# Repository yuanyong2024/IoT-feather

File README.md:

### This is a BG95 EVB in adafruit feather form-factor.
### It can be developed by quecpython, similar to circuit python

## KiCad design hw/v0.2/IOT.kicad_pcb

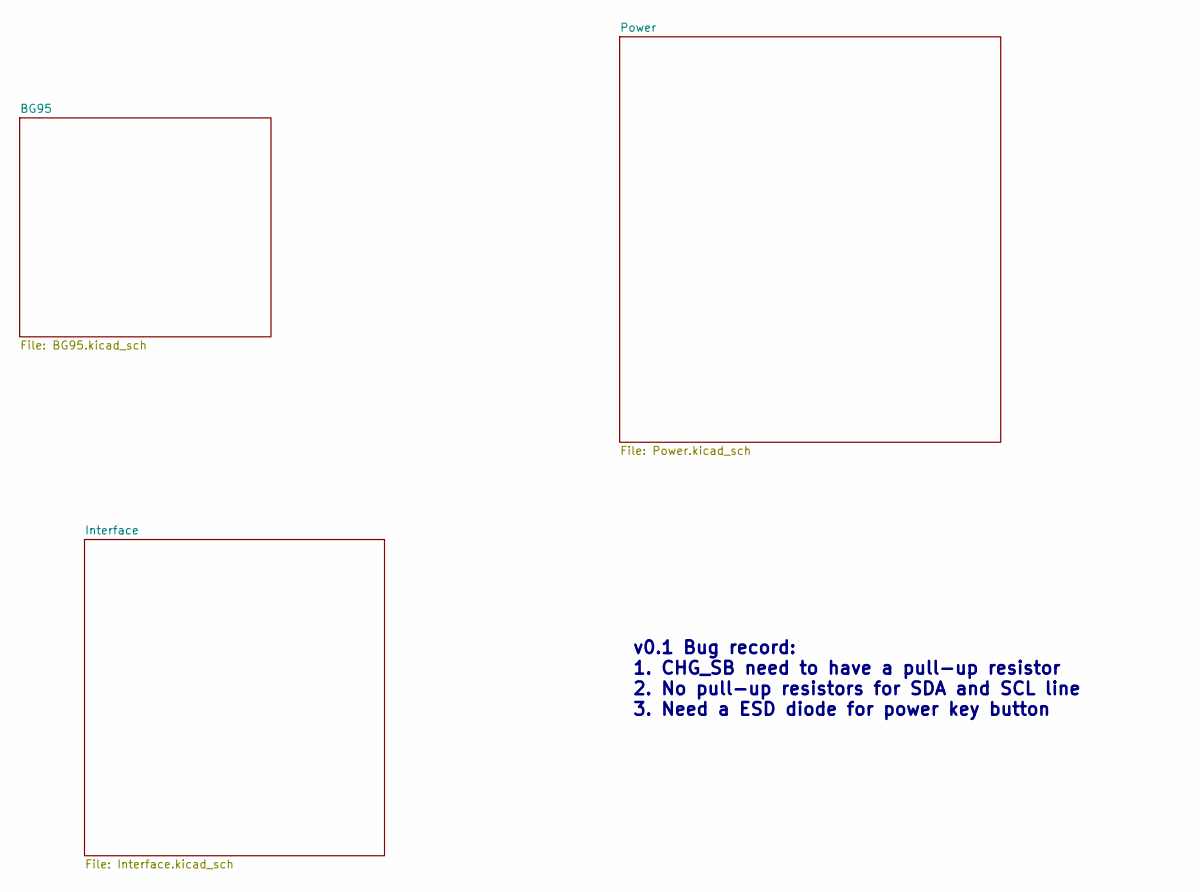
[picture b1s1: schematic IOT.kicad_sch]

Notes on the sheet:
v0.1 Bug record: 1. CHG_SB need to have a pull-up resistor 2. No pull-up resistors for SDA and SCL line 3. Need a ESD diode for power key button

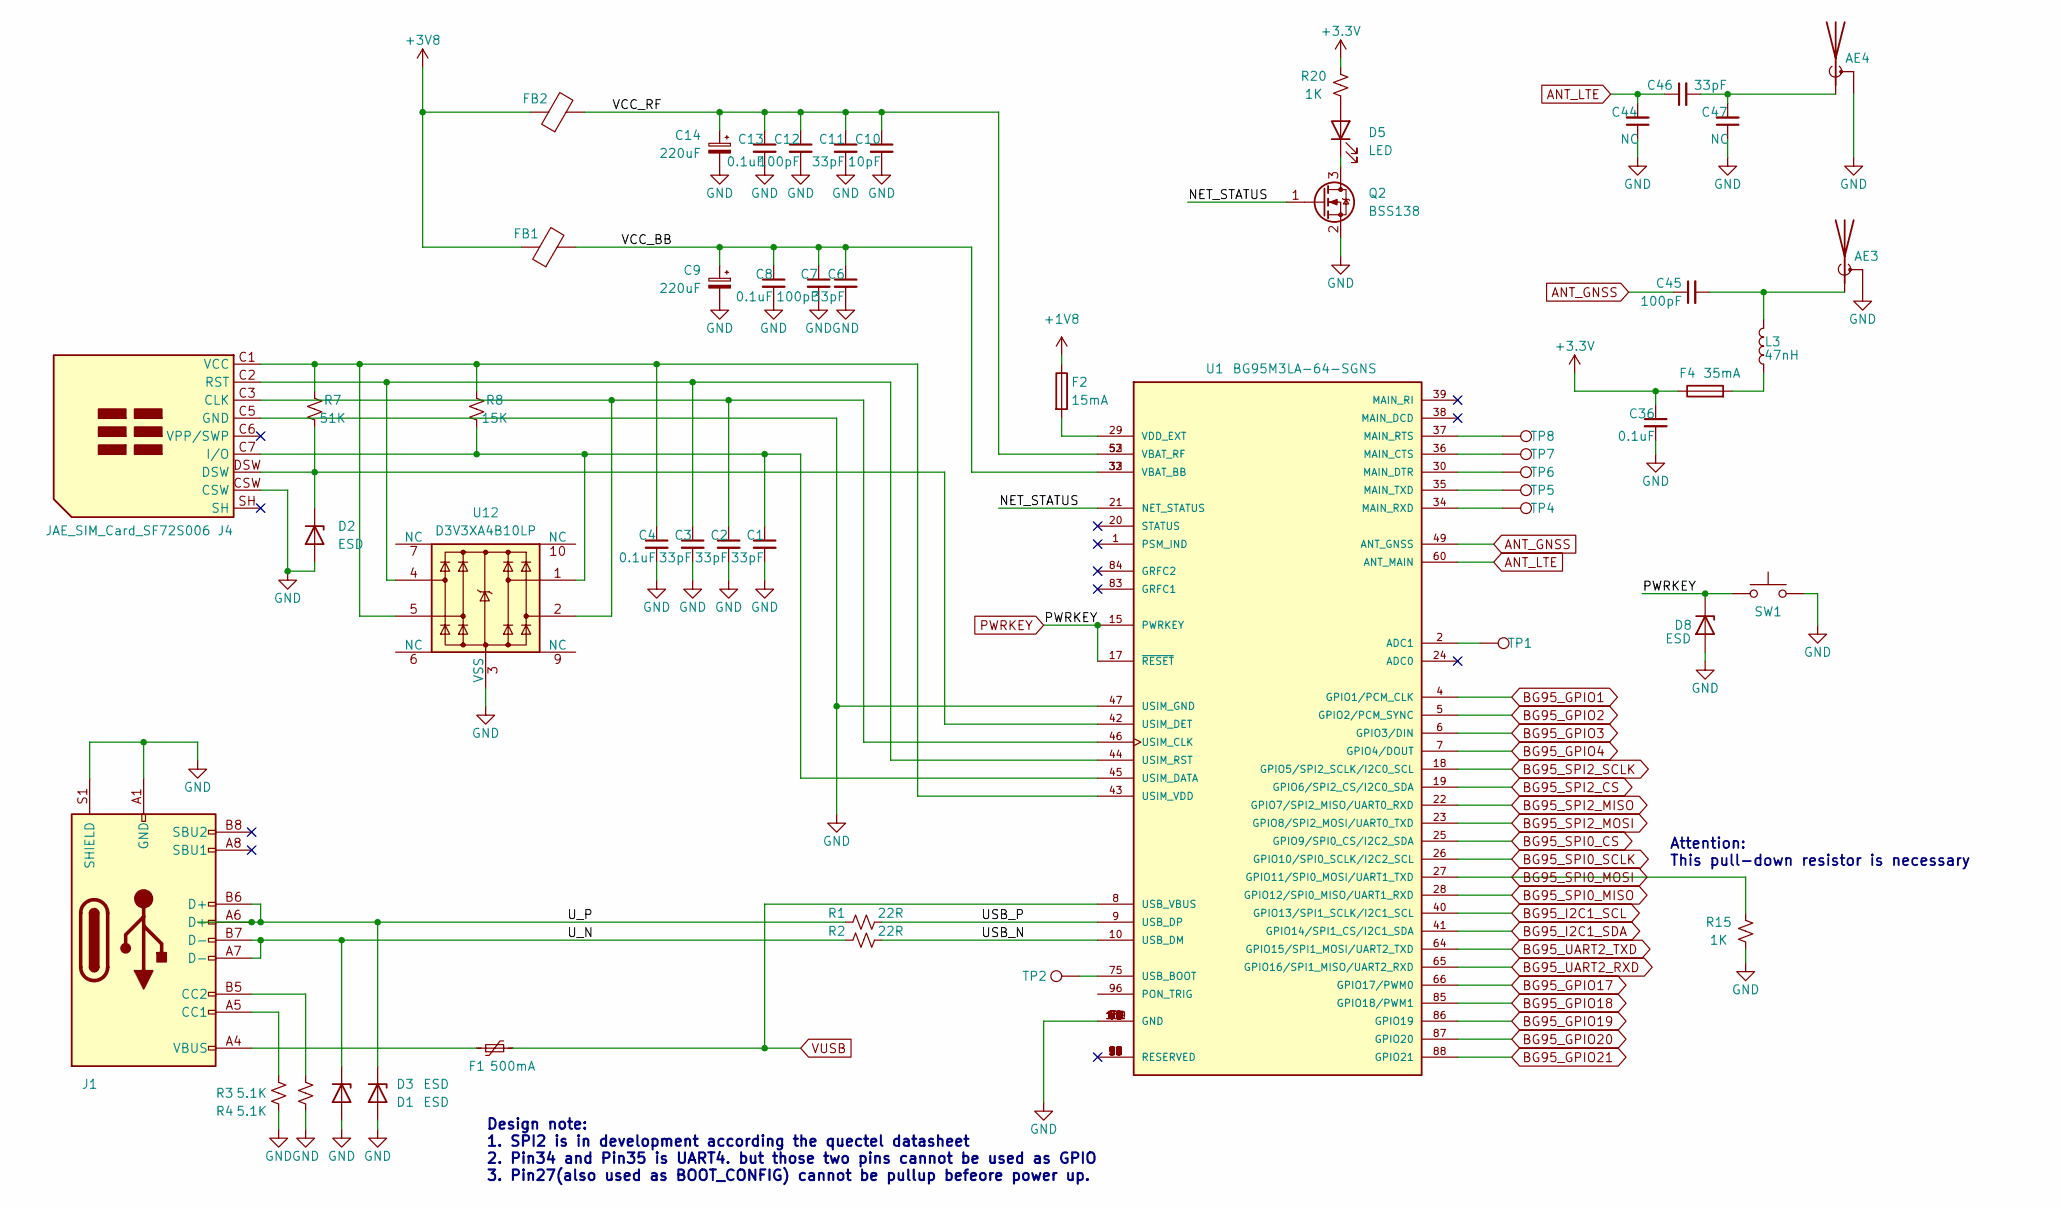
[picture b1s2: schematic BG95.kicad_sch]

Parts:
AE3, AE4: Antenna_Shield; U.FL_Hirose_U.FL-R-SMT-1_Vertical
C1, C2, C3, C6, C11: 33pF; C_0402_1005Metric
C4, C8, C13, C36: 0.1uF; C_0402_1005Metric
C7, C12: 100pF; C_0402_1005Metric
C9, C14: 220uF; CP_EIA-3528-12_Kemet-T
C10: 10pF; C_0402_1005Metric
C44, C47: NC; C_0201_0603Metric
C45: 100pF; C_0201_0603Metric
C46: 33pF; C_0201_0603Metric
D1, D2, D3: ESD; D_SOD-923
D5: LED; LED_0603_1608Metric
D8: ESD; D_SOD-523
F1: 500mA; Fuse_0603_1608Metric
F2: 15mA; Fuse_0402_1005Metric
F4: 35mA; Fuse_0402_1005Metric
FB1, FB2: L_0603_1608Metric
J1: USB_C_Receptacle_USB2.0; USB_C_Receptacle_HRO_TYPE-C-31-M-12
J4: JAE_SIM_Card_SF72S006
L3: 47nH; L_0402_1005Metric
Q2: BSS138; SOT-523
R1, R2: 22R; R_0402_1005Metric
R3, R4: 5.1K; R_0402_1005Metric
R7: 51K; R_0402_1005Metric
R8: 15K; R_0402_1005Metric
R15, R20: 1K; R_0402_1005Metric
SW1: SW_Omron_B3FS; SW_Push_SPST_NO_Alps_SKRK
TP1, TP2, TP4, TP5, TP6, TP7, TP8: TestPoint; TestPoint_Pad_D1.0mm
U1: BG95M3LA-64-SGNS; XCVR_BG95M3LA-64-SGNS
U12: D3V3XA4B10LP; Diodes_UDFN-10_1.0x2.5mm_P0.5mm

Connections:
+1V8: F2.1; also elsewhere on the board
+3V8: FB1.1, FB2.1; also elsewhere on the board
/BG95/NET_STATUS: Q2.1 (G), U1.21 (NET_STATUS)
/BG95/USB_N: R2.2, U1.10 (USB_DM)
/BG95/USB_P: R1.2, U1.9 (USB_DP)
/BG95/U_N: D1.1 (K), J1.A7 (D-), J1.B7 (D-), R2.1
/BG95/U_P: D3.1 (K), J1.A6 (D+), J1.B6 (D+), R1.1
/BG95/VCC_BB: C6.1, C7.1, C8.1, C9.1, FB1.2, U1.32 (VBAT_BB), U1.33 (VBAT_BB)
/BG95/VCC_RF: C10.1, C11.1, C12.1, C13.1, C14.1, FB2.2, U1.52 (VBAT_RF), U1.53 (VBAT_RF)
ANT_GNSS: C45.1, U1.49 (ANT_GNSS)
ANT_LTE: C44.2, C46.1, U1.60 (ANT_MAIN)
BG95_GPIO1: U1.4 (GPIO1/PCM_CLK); also elsewhere on the board
BG95_GPIO2: U1.5 (GPIO2/PCM_SYNC); also elsewhere on the board
BG95_GPIO3: U1.6 (GPIO3/DIN); also elsewhere on the board
BG95_GPIO4: U1.7 (GPIO4/DOUT); also elsewhere on the board
BG95_GPIO17: U1.66 (GPIO17/PWM0); also elsewhere on the board
BG95_GPIO18: U1.85 (GPIO18/PWM1); also elsewhere on the board
BG95_GPIO19: U1.86 (GPIO19); also elsewhere on the board
BG95_GPIO20: U1.87 (GPIO20); also elsewhere on the board
BG95_GPIO21: U1.88 (GPIO21); also elsewhere on the board
BG95_I2C1_SCL: U1.40 (GPIO13/SPI1_SCLK/I2C1_SCL); also elsewhere on the board
BG95_I2C1_SDA: U1.41 (GPIO14/SPI1_CS/I2C1_SDA); also elsewhere on the board
BG95_SPI0_CS: U1.25 (GPIO9/SPI0_CS/I2C2_SDA); also elsewhere on the board
BG95_SPI0_MISO: U1.28 (GPIO12/SPI0_MISO/UART1_RXD); also elsewhere on the board
BG95_SPI0_MOSI: R15.1, U1.27 (GPIO11/SPI0_MOSI/UART1_TXD); also elsewhere on the board
BG95_SPI0_SCLK: U1.26 (GPIO10/SPI0_SCLK/I2C2_SCL); also elsewhere on the board
BG95_SPI2_CS: U1.19 (GPIO6/SPI2_CS/I2C0_SDA); also elsewhere on the board
BG95_SPI2_MISO: U1.22 (GPIO7/SPI2_MISO/UART0_RXD); also elsewhere on the board
BG95_SPI2_MOSI: U1.23 (GPIO8/SPI2_MOSI/UART0_TXD); also elsewhere on the board
BG95_SPI2_SCLK: U1.18 (GPIO5/SPI2_SCLK/I2C0_SCL); also elsewhere on the board
BG95_UART2_RXD: U1.65 (GPIO16/SPI1_MISO/UART2_RXD); also elsewhere on the board
BG95_UART2_TXD: U1.64 (GPIO15/SPI1_MOSI/UART2_TXD); also elsewhere on the board
GND: AE3.2 (Shield), AE4.2 (Shield), C1.2, C2.2, C3.2, C4.2, C6.2, C7.2, C8.2, C9.2, C10.2, C11.2, C12.2, C13.2, C14.2, C36.2, C44.1, C47.1, D1.2 (A), D2.2 (A), D3.2 (A), D8.2 (A), J1.A1 (GND), J1.A12 (GND), J1.B1 (GND), J1.B12 (GND), J1.S1 (SHIELD), J4.C5 (GND), J4.CSW, Q2.2 (S), R3.1, R4.1, R15.2, SW1.2, U1.3 (GND), U1.31 (GND), U1.47 (USIM_GND), U1.48 (GND), U1.50 (GND), U1.54 (GND), U1.55 (GND), U1.58 (GND), U1.59 (GND), U1.61 (GND), U1.62 (GND), U1.67 (GND), U1.68 (GND), U1.69 (GND), U1.70 (GND), U1.71 (GND), U1.72 (GND), U1.73 (GND), U1.74 (GND), U1.79 (GND), U1.80 (GND), U1.81 (GND), U1.82 (GND), U1.89 (GND), U1.90 (GND), U1.91 (GND), U1.100 (GND), U1.101 (GND), U1.102 (GND), U12.3 (VSS), U12.8 (VSS); also elsewhere on the board
unnamed: AE3.1 (A), C45.2, L3.1
unnamed: AE4.1 (A), C46.2, C47.2
unnamed: D2.1 (K), J4.DSW, R7.1, U1.42 (USIM_DET)
unnamed: D5.2 (A), R20.2
unnamed: D5.1 (K), Q2.3 (D)
unnamed: F1.1, J1.A4 (VBUS), J1.A9 (VBUS), J1.B4 (VBUS), J1.B9 (VBUS)
unnamed: J1.A5 (CC1), R3.2
unnamed: J1.B5 (CC2), R4.2
unnamed: C2.1, J4.C3 (CLK), U1.46 (USIM_CLK), U12.2
unnamed: C1.1, J4.C7 (I/O), R8.1, U1.45 (USIM_DATA), U12.1
unnamed: C3.1, J4.C2 (RST), U1.44 (USIM_RST), U12.4
unnamed: C4.1, J4.C1 (VCC), R7.2, R8.2, U1.43 (USIM_VDD), U12.5
unnamed: TP1.1, U1.2 (ADC1)
unnamed: TP7.1, U1.36 (MAIN_CTS)
unnamed: TP6.1, U1.30 (MAIN_DTR)
unnamed: TP8.1, U1.37 (MAIN_RTS)
unnamed: TP4.1, U1.34 (MAIN_RXD)
unnamed: TP5.1, U1.35 (MAIN_TXD)
unnamed: TP2.1, U1.75 (USB_BOOT)
unnamed: F2.2, U1.29 (VDD_EXT)
PWRKEY: D8.1 (K), SW1.1, U1.15 (PWRKEY), U1.17 (~RESET); also elsewhere on the board
VUSB: F1.2, U1.8 (USB_VBUS); also elsewhere on the board

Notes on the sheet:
Attention: This pull-down resistor is necessary
Design note: 1. SPI2 is in development according the quectel datasheet 2. Pin34 and Pin35 is UART4. but those two pins cannot be used as GPIO 3. Pin27(also used as BOOT_CONFIG) cannot be pullup befeore power up.

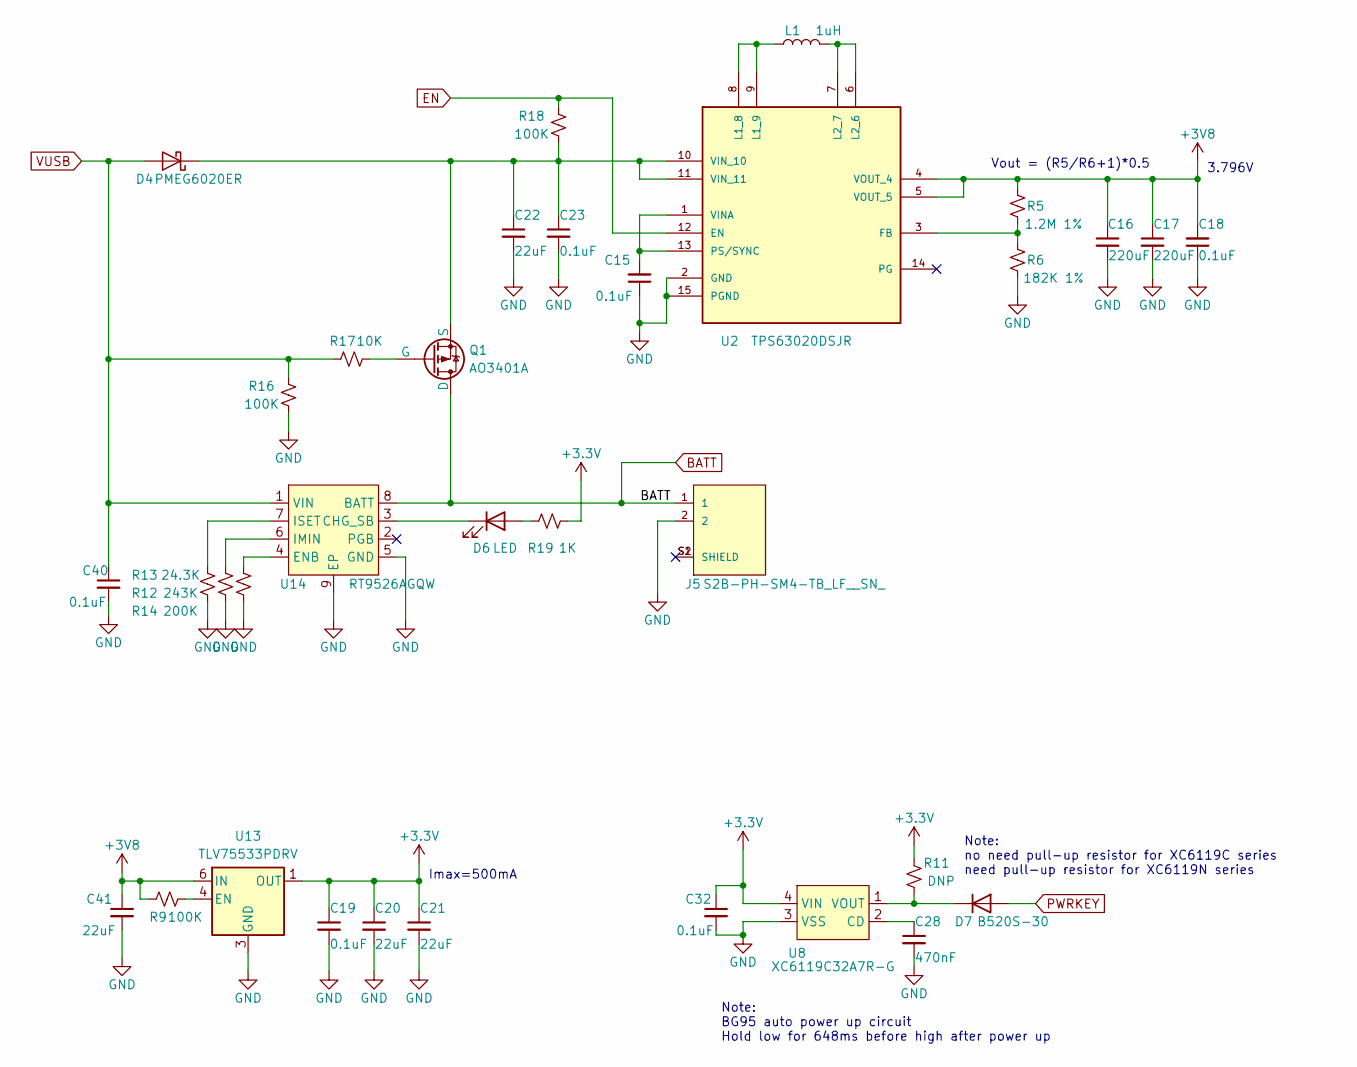
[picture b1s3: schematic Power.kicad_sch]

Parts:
C15, C18, C32, C40: 0.1uF; C_0402_1005Metric
C16, C17: 220uF; CP_EIA-3528-12_Kemet-T
C19, C23: 0.1uF; C_0603_1608Metric
C20, C21, C22, C41: 22uF; C_0603_1608Metric
C28: 470nF; C_0402_1005Metric
D4: PMEG6020ER; D_SOD-123
D6: LED; LED_0603_1608Metric
D7: B520S-30; D_SOD-523
J5: S2B-PH-SM4-TB_LF__SN_; JST_S2B-PH-SM4-TB_LF__SN_
L1: 1uH; L_Bourns-SRN4018
Q1: AO3401A; SOT-23
R5: 1.2M 1%; R_0402_1005Metric
R6: 182K 1%; R_0402_1005Metric
R9, R16, R18: 100K; R_0402_1005Metric
R11: DNP; R_0402_1005Metric
R12: 243K; R_0402_1005Metric
R13: 24.3K; R_0402_1005Metric
R14: 200K; R_0402_1005Metric
R17: 10K; R_0402_1005Metric
R19: 1K; R_0402_1005Metric
U2: TPS63020DSJR; IC_TPS63020DSJR
U8: XC6119C32A7R-G; USPN-4
U13: TLV75533PDRV; WSON-6-1EP_2x2mm_P0.65mm_EP1x1.6mm
U14: RT9526AGQW; DFN-8-1EP_3x2mm_P0.5mm_EP1.7x1.4mm

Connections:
+3V8: C16.1, C17.1, C18.2, C41.1, R5.2, R9.2, U2.4 (VOUT_4), U2.5 (VOUT_5), U13.6 (IN); also elsewhere on the board
BATT: J5.1, Q1.3 (D), U14.8 (BATT); also elsewhere on the board
EN: R18.1, U2.12 (EN); also elsewhere on the board
GND: C15.1, C16.2, C17.2, C18.1, C19.2, C20.2, C21.2, C22.2, C23.2, C28.2, C32.2, C40.2, C41.2, J5.2, R6.1, R12.2, R13.2, R14.2, R16.2, U2.2 (GND), U2.15 (PGND), U8.3 (VSS), U13.3 (GND), U13.7 (GND), U14.5 (GND), U14.9 (EP); also elsewhere on the board
unnamed: C22.1, C23.1, D4.1 (K), Q1.2 (S), R18.2, U2.10 (VIN_10), U2.11 (VIN_11)
unnamed: D6.2 (A), R19.2
unnamed: D6.1 (K), U14.3 (CHG_SB)
unnamed: D7.1 (K), R11.2, U8.1 (VOUT)
unnamed: Q1.1 (G), R17.2
unnamed: R5.1, R6.2, U2.3 (FB)
unnamed: L1.1, U2.8 (L1_8), U2.9 (L1_9)
unnamed: L1.2, U2.6 (L2_6), U2.7 (L2_7)
unnamed: C15.2, U2.1 (VINA), U2.13 (PS/SYNC)
unnamed: C28.1, U8.2 (CD)
unnamed: R9.1, U13.4 (EN)
unnamed: R14.1, U14.4 (ENB)
unnamed: R12.1, U14.6 (IMIN)
unnamed: R13.1, U14.7 (ISET)
PWRKEY: D7.2 (A); also elsewhere on the board
VUSB: C40.1, D4.2 (A), R16.1, R17.1, U14.1 (VIN); also elsewhere on the board

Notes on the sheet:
Vout = (R5/R6+1)*0.5
Imax=500mA
Note: BG95 auto power up circuit Hold low for 648ms before high after power up
3.796V
Note: no need pull-up resistor for XC6119C series need pull-up resistor for XC6119N series

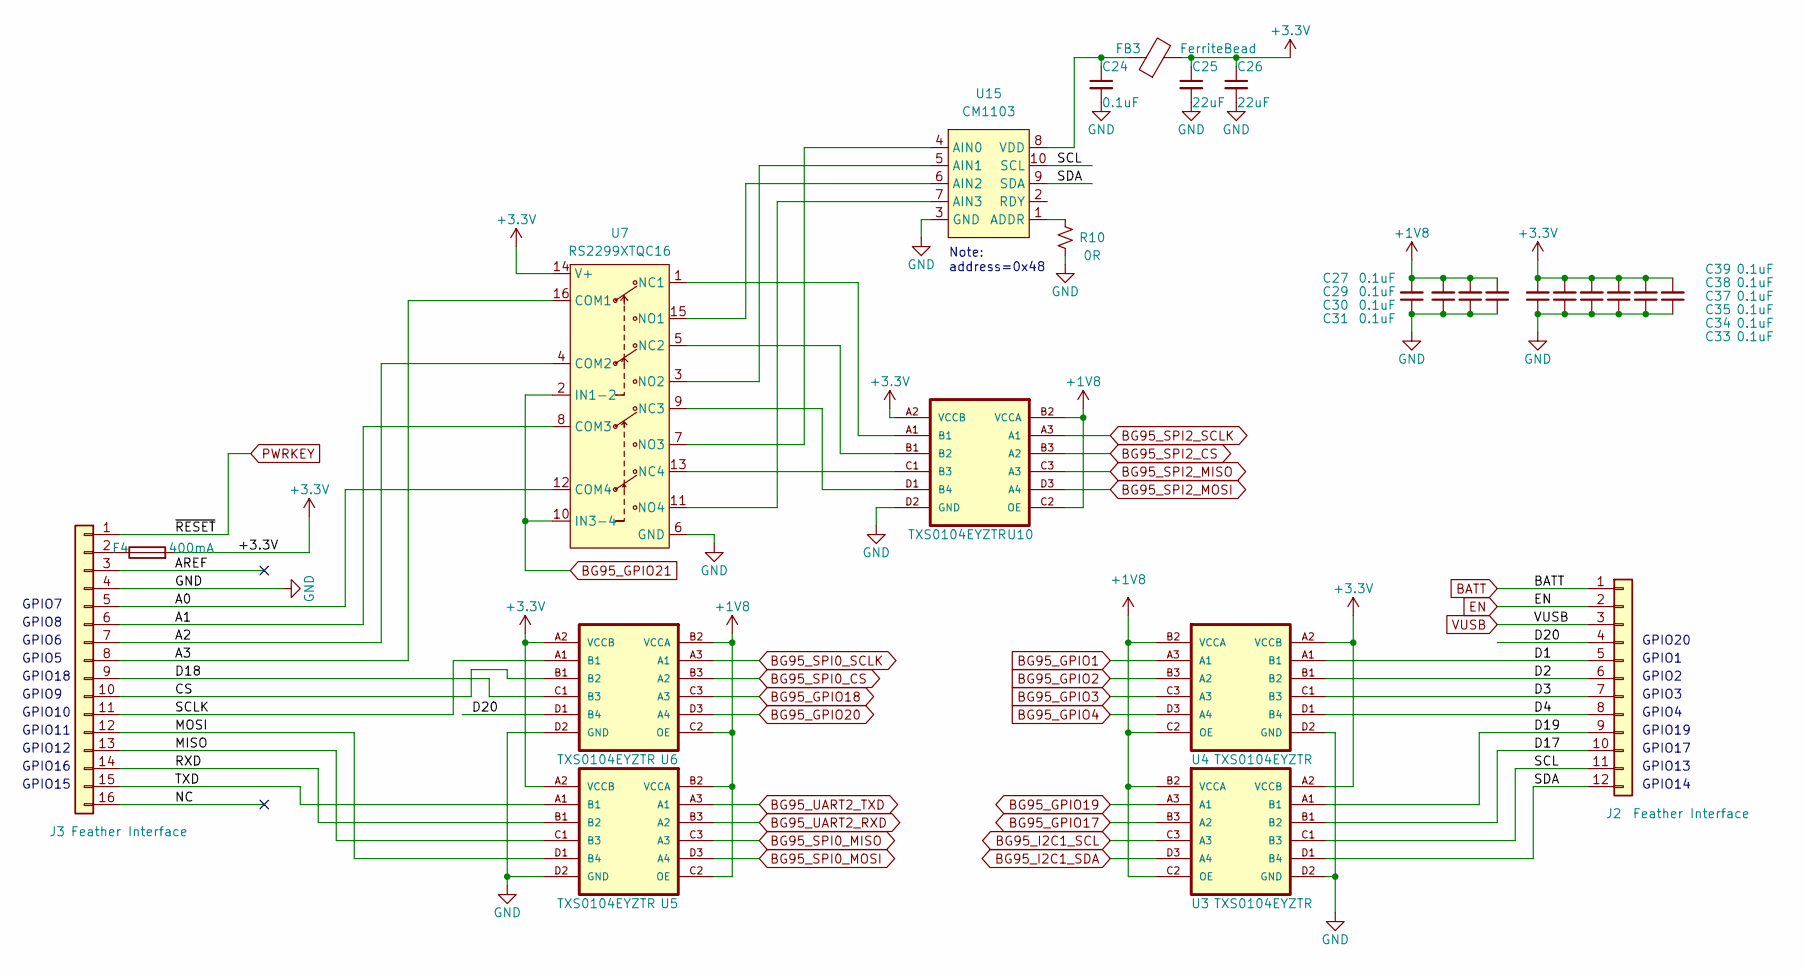
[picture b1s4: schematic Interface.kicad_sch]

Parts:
C24, C27, C29, C30, C31, C33, C34, C35, C37, C38, C39: 0.1uF; C_0402_1005Metric
C25, C26: 22uF; C_0402_1005Metric
F4: 400mA; Fuse_0603_1608Metric
FB3: FerriteBead; L_0402_1005Metric
J2: Feather Interface; PinHeader_1x12_P2.54mm_Vertical_SMD_Pin1Left
J3: Feather Interface; PinHeader_1x16_P2.54mm_Vertical_SMD_Pin1Right
R10: 0R; R_0201_0603Metric
U3, U4, U5, U6, U10: TXS0104EYZTR; BGA12N50P4X3_186X136X62N
U7: RS2299XTQC16; QFN-16-1EP_3x3mm_P0.5mm_EP1.75x1.75mm
U15: CM1103; CM1103-QFNTA

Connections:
+1V8: C27.2, C29.2, C30.2, C31.2, U3.B2 (VCCA), U3.C2 (OE), U4.B2 (VCCA), U4.C2 (OE), U5.B2 (VCCA), U5.C2 (OE), U6.B2 (VCCA), U6.C2 (OE), U10.B2 (VCCA), U10.C2 (OE); also elsewhere on the board
/Interface/A0: J3.5, U7.12 (COM4)
/Interface/A1: J3.6, U7.8 (COM3)
/Interface/A2: J3.7, U7.4 (COM2)
/Interface/A3: J3.8, U7.16 (COM1)
/Interface/AREF: J3.3
/Interface/CS: J3.10, U6.B1 (B2)
/Interface/D1: J2.5, U4.A1 (B1)
/Interface/D2: J2.6, U4.B1 (B2)
/Interface/D3: J2.7, U4.C1 (B3)
/Interface/D4: J2.8, U4.D1 (B4)
/Interface/D17: J2.10, U3.B1 (B2)
/Interface/D18: J3.9, U6.C1 (B3)
/Interface/D19: J2.9, U3.A1 (B1)
/Interface/D20: J2.4, U6.D1 (B4)
/Interface/MISO: J3.13, U5.C1 (B3)
/Interface/MOSI: J3.12, U5.D1 (B4)
/Interface/NC: J3.16
/Interface/RXD: J3.14, U5.B1 (B2)
/Interface/SCL: J2.11, U3.C1 (B3), U15.10 (SCL)
/Interface/SCLK: J3.11, U6.A1 (B1)
/Interface/SDA: J2.12, U3.D1 (B4), U15.9 (SDA)
/Interface/TXD: J3.15, U5.A1 (B1)
BATT: J2.1; also elsewhere on the board
BG95_GPIO1: U4.A3 (A1); also elsewhere on the board
BG95_GPIO2: U4.B3 (A2); also elsewhere on the board
BG95_GPIO3: U4.C3 (A3); also elsewhere on the board
BG95_GPIO4: U4.D3 (A4); also elsewhere on the board
BG95_GPIO17: U3.B3 (A2); also elsewhere on the board
BG95_GPIO18: U6.C3 (A3); also elsewhere on the board
BG95_GPIO19: U3.A3 (A1); also elsewhere on the board
BG95_GPIO20: U6.D3 (A4); also elsewhere on the board
BG95_GPIO21: U7.2 (IN1-2), U7.10 (IN3-4); also elsewhere on the board
BG95_I2C1_SCL: U3.C3 (A3); also elsewhere on the board
BG95_I2C1_SDA: U3.D3 (A4); also elsewhere on the board
BG95_SPI0_CS: U6.B3 (A2); also elsewhere on the board
BG95_SPI0_MISO: U5.C3 (A3); also elsewhere on the board
BG95_SPI0_MOSI: U5.D3 (A4); also elsewhere on the board
BG95_SPI0_SCLK: U6.A3 (A1); also elsewhere on the board
BG95_SPI2_CS: U10.B3 (A2); also elsewhere on the board
BG95_SPI2_MISO: U10.C3 (A3); also elsewhere on the board
BG95_SPI2_MOSI: U10.D3 (A4); also elsewhere on the board
BG95_SPI2_SCLK: U10.A3 (A1); also elsewhere on the board
BG95_UART2_RXD: U5.B3 (A2); also elsewhere on the board
BG95_UART2_TXD: U5.A3 (A1); also elsewhere on the board
EN: J2.2; also elsewhere on the board
GND: C24.2, C25.2, C26.2, C27.1, C29.1, C30.1, C31.1, C33.1, C34.1, C35.1, C37.1, C38.1, C39.1, J3.4, R10.2, U3.D2 (GND), U4.D2 (GND), U5.D2 (GND), U6.D2 (GND), U7.6 (GND), U10.D2 (GND), U15.3 (GND); also elsewhere on the board
unnamed: U7.1 (NC1), U10.A1 (B1)
unnamed: U7.5 (NC2), U10.B1 (B2)
unnamed: U7.13 (NC4), U10.C1 (B3)
unnamed: U7.9 (NC3), U10.D1 (B4)
unnamed: R10.1, U15.1 (ADDR)
unnamed: U7.7 (NO3), U15.4 (AIN0)
unnamed: U7.3 (NO2), U15.5 (AIN1)
unnamed: U7.15 (NO1), U15.6 (AIN2)
unnamed: U7.11 (NO4), U15.7 (AIN3)
unnamed: C24.1, FB3.1, U15.8 (VDD)
PWRKEY: J3.1; also elsewhere on the board
VUSB: J2.3; also elsewhere on the board

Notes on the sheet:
GPIO8
GPIO10
GPIO9
GPIO13
GPIO14
GPIO12
GPIO3
GPIO18
GPIO5
GPIO4
Note: address=0x48
GPIO6
GPIO20
GPIO17
GPIO15
GPIO16
GPIO2
GPIO19
GPIO1
GPIO7
GPIO11

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
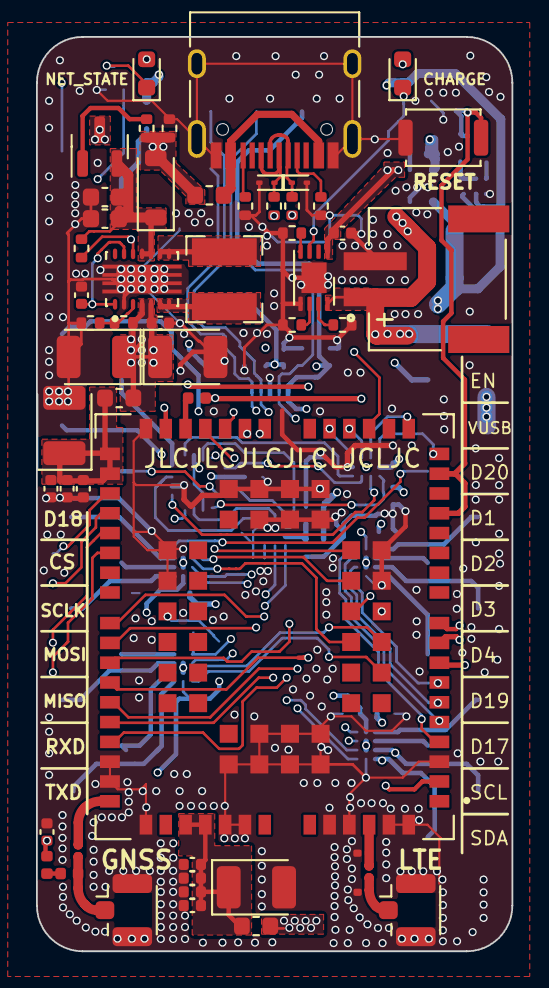
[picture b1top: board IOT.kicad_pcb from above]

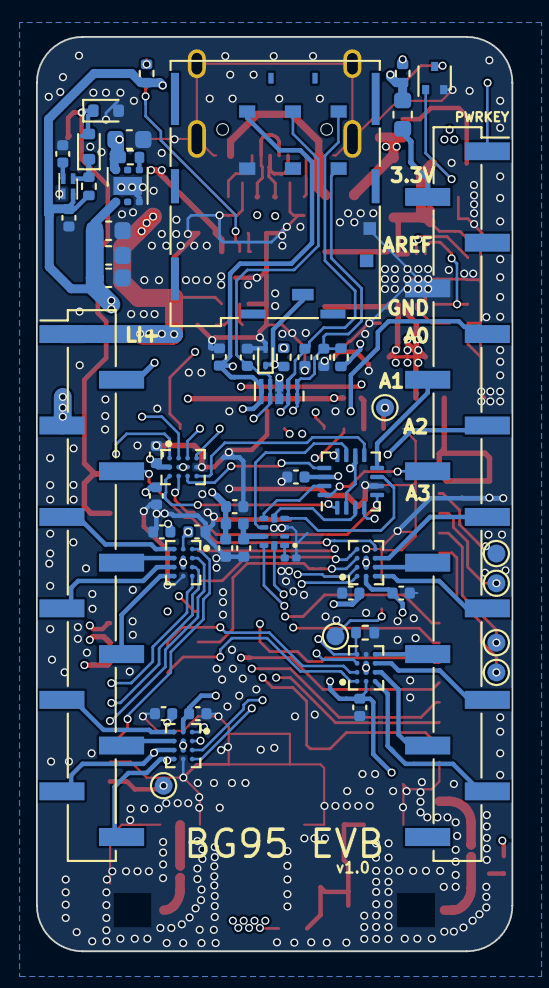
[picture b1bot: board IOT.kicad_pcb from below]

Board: 4 copper layers, 26.4 x 50.8 mm, 111 parts (57 on the bottom side), 104 nets.

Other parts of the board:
F3: 400mA; Fuse_0603_1608Metric

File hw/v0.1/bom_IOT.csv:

Ref,Qnty,Value,Footprint,PN,
"AE3, AE4",2,Antenna_Shield,Connector_Coaxial:U.FL_Hirose_U.FL-R-SMT-1_Vertical,,
"C1, C2, C3, C6, C11",5,33pF,Capacitor_SMD:C_0402_1005Metric,CC0402JRNPO9BN330,100
"C4, C8, C13, C15, C18, C24, C27, C29, C30, C31, C32, C33, C34, C35, C36, C37, C38, C39, C40",19,0.1uF,Capacitor_SMD:C_0402_1005Metric,0402F104M500NT,500
"C5, C10",2,10pF,Capacitor_SMD:C_0402_1005Metric,GRM1555C1H100JA01D,100
"C7, C12",2,100pF,Capacitor_SMD:C_0402_1005Metric,0402CG101J500NT,100
"C9, C14, C16, C17",4,220uF,Capacitor_Tantalum_SMD:CP_EIA-3528-12_Kemet-T,,
"C19, C23",2,0.1uF,Capacitor_SMD:C_0603_1608Metric,CC06033KRXX7RBB104,100
"C20, C21, C22, C41",4,22uF,Capacitor_SMD:C_0603_1608Metric,CL10A226MQ8NRNC,100
"C25, C26",2,22uF,Capacitor_SMD:C_0402_1005Metric,GRM155R60J226ME11D,10
C28,1,470nF,Capacitor_SMD:C_0402_1005Metric,CL05A474KP5NNNC,100
"C44, C47",2,NC,Capacitor_SMD:C_0201_0603Metric,,
C45,1,100pF,Capacitor_SMD:C_0201_0603Metric,GRM0335C1H101JA01D,100
C46,1,33pF,Capacitor_SMD:C_0201_0603Metric,GRM0335C1H330JA01D,100
"D1, D2, D3",3,ESD,Diode_SMD:D_SOD-923,ESD9B3.3ST5G,8
D4,1,PMEG6020ER,Diode_SMD:D_SOD-123,"PMEG6020ER,115",5
"D5, D6",2,LED,LED_SMD:LED_0603_1608Metric,,
D7,1,B520S-30,Diode_SMD:D_SOD-523,RB520S-30,50
F1,1,500mA,Fuse:Fuse_0603_1608Metric,MF-FSMF050X-2,20
F2,1,15mA,Fuse:Fuse_0402_1005Metric,PRG15BC330MM1RC,5
F3,1,400mA,Fuse:Fuse_0603_1608Metric,0603L040/24AR,5
F4,1,38mA,Fuse:Fuse_0402_1005Metric,PRG15BC330MM1RC,3
"FB1, FB2",2,~,Inductor_SMD:L_0603_1608Metric,YI160808U300-5R0T,50
FB3,1,FerriteBead,Inductor_SMD:L_0402_1005Metric,BLM15PD121SN1D,100
J1,1,USB_C_Receptacle_USB2.0,Connector_USB:USB_C_Receptacle_HRO_TYPE-C-31-M-12,,
J2,1,Feather Interface,Connector_PinHeader_2.54mm:PinHeader_1x12_P2.54mm_Vertical_SMD_Pin1Left,,
J3,1,Feather Interface,Connector_PinHeader_2.54mm:PinHeader_1x16_P2.54mm_Vertical_SMD_Pin1Right,,
J4,1,JAE_SIM_Card_SF72S006,Connector_JAE:JAE_SIM_Card_SF72S006,,
J5,1,S2B-PH-SM4-TB_LF__SN_,myfootprintlib:JST_S2B-PH-SM4-TB_LF__SN_,,
L1,1,1uH,Inductor_SMD:L_Bourns-SRN4018,YSMC0420V-1R0M,1
L3,1,47nH,Inductor_SMD:L_0402_1005Metric,LQG15HS47NJ02D,100
Q1,1,AO3401A,Package_TO_SOT_SMD:SOT-23,AO3401A,10
"Q2, Q3",2,BSS138,Package_TO_SOT_SMD:SOT-523,,
"R1, R2",2,22R,Resistor_SMD:R_0402_1005Metric,00402WGF220JTCE,100
"R3, R4",2,5.1K,Resistor_SMD:R_0402_1005Metric,0402WGF5101TCE,100
R5,1,1.2M 1%,Resistor_SMD:R_0402_1005Metric,0402WGF1204TCE,100
R6,1,182K 1%,Resistor_SMD:R_0402_1005Metric,0402WGF1823TCE,100
R7,1,51K,Resistor_SMD:R_0402_1005Metric,0402WGF5102TCE,100
R8,1,15K,Resistor_SMD:R_0402_1005Metric,0402WGF1502TCE,100
"R9, R15, R16, R18",4,100K,Resistor_SMD:R_0402_1005Metric,RC-02W1003FT,100
R10,1,0R,Resistor_SMD:R_0201_0603Metric,RC0201JR-070RL,1000
R11,1,DNP,Resistor_SMD:R_0402_1005Metric,,
R12,1,243K,Resistor_SMD:R_0402_1005Metric,FRC0402F2433TS,100
R13,1,24.3K,Resistor_SMD:R_0402_1005Metric,0402WGF2432TCE,100
R14,1,200K,Resistor_SMD:R_0402_1005Metric,0402WGF2003TCE,100
R17,1,10K,Resistor_SMD:R_0402_1005Metric,0402WGF1002TCE,1000
"R19, R20",2,1K,Resistor_SMD:R_0402_1005Metric,RC-02W102JT,100
SW1,1,SW_Omron_B3FS,Button_Switch_SMD:SW_Push_SPST_NO_Alps_SKRK,,
"TP2, TP4, TP5, TP6, TP7, TP8",6,TestPoint,TestPoint:TestPoint_Pad_D1.0mm,,
U1,1,BG95M3LA-64-SGNS,myfootprintlib:XCVR_BG95M3LA-64-SGNS,,
U2,1,TPS63020DSJR,myfootprintlib:IC_TPS63020DSJR,TPS63020DSJR,1
"U3, U4, U5, U6, U10",5,TXS0104EYZTR,myfootprintlib:BGA12N50P4X3_186X136X62N,TXS0104EYZTR,5
U7,1,RS2299XTQC16,Package_DFN_QFN:QFN-16-1EP_3x3mm_P0.5mm_EP1.75x1.75mm,RS2299XTQC16,1
U8,1,XC6119C32A7R-G,kiCadPcbLib:USPN-4,XC6119C32A7R-G,
U12,1,D3V3XA4B10LP,Package_DFN_QFN:Diodes_UDFN-10_1.0x2.5mm_P0.5mm,D3V3XA4B10LP-7,9
U13,1,TLV75533PDRV,Package_SON:WSON-6-1EP_2x2mm_P0.65mm_EP1x1.6mm,TLV75533PDRV,5
U14,1,RT9526AGQW,Package_DFN_QFN:DFN-8-1EP_3x2mm_P0.5mm_EP1.7x1.4mm,,
U15,1,CM1103,myfootprintlib:CM1103-QFNTA,CM1103-QFNTA,1

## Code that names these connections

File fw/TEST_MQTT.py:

'''
from machine import Pin
import utime
from machine import UART

uart2 = UART(UART.UART2, 115200, 8, 0, 1, 0)

pinTable=[Pin.GPIO1,Pin.GPIO2,Pin.GPIO3,Pin.GPIO4,Pin.GPIO5,Pin.GPIO6,Pin.GPIO7,Pin.GPIO8,Pin.GPIO9,Pin.GPIO10,Pin.GPIO11,Pin.GPIO12,Pin.GPIO13,Pin.GPIO14,Pin.GPIO15,Pin.GPIO16,Pin.GPIO17,Pin.GPIO18,Pin.GPIO19,Pin.GPIO20]
'''

'''
@Author: Baron
@Date: 2020-04-24
@LastEditTime: 2020-04-24 17:06:08
@Description: example for module umqtt
@FilePath: example_mqtt_file.py
'''
from umqtt import MQTTClient
import utime
import log
import checkNet
from machine import Pin
from machine import I2C 
import misc

from usr.CM1103 import *
import quecgnss


PROJECT_NAME = "QuecPython_MQTT_example"
PROJECT_VERSION = "1.0.0"

checknet = checkNet.CheckNetwork(PROJECT_NAME, PROJECT_VERSION)


log.basicConfig(level=log.INFO)
mqtt_log = log.getLogger("MQTT")


state = 0

def sub_cb(topic, msg):
    global state
    mqtt_log.info("Subscribe Recv: Topic={},Msg={}".format(topic.decode(), msg.decode()))
    state = 1


'''
analogSwitch = Pin(Pin.GPIO21,Pin.OUT,Pin.PULL_DISABLE,1)
i2c_obj = I2C(I2C.I2C1, I2C.STANDARD_MODE)
adc = CM1103(i2c_obj)
adc.write_config(mode=MODE.CONTINIOUS,mux=MUX.MUX_A0_GND,pga=PGA.PGA_4096)
print(adc.analogRead(A0))
'''

#important notice
#when trying to debug with MQTTX broker. it sometimes may show up something like The Broker has actively disconnected, Reason: Session taken over (Code: 142)
#and one solution is click the timestamp icom on Cline ID location so that everything clicked a connect, it's a new connection and then it will not taken over by previous connection.
if __name__ == '__main__':
    stagecode, subcode = checknet.wait_network_connected(30)
    if stagecode == 3 and subcode == 1:
        mqtt_log.info('Network connection successful!')

        # 创建一个mqtt实例
        c = MQTTClient("mqttx_yuanyong2024", "broker.emqx.io", 1883)
        #c = MQTTClient("umqtt_client", "mq.tongxinmao.com", 18830)
        # 设置消息回调
        c.set_callback(sub_cb)
        #建立连接
        c.connect()
        # 订阅主题
        c.subscribe(b"/public/quecpython")
        mqtt_log.info("Connected to mq.tongxinmao.com, subscribed to /public/TEST/quecpython topic" )
        # 发布消息
        retry = 5
        while True:
            c.publish(b"/public/TEST/quecpython", b"my name is Quecpython!")
            mqtt_log.info("Publish topic: /public/TEST/quecpython, msg: my name is Quecpython")
            c.wait_msg()  #阻塞函数，监听消息
            utime.sleep(1)
            retry-=1
            if retry==0:
                break
        # 关闭连接
        c.disconnect()
    else:
        mqtt_log.info('Network connection failed! stagecode = {}, subcode = {}'.format(stagecode, subcode))

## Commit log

2024-09-16 initial commit for IoT_feather
2024-09-29 reorganize the folder and add ADC driver in
2025-05-04 update the quecpython project
